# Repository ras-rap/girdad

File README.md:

# GIrDAd

A modern USB-C dongle/device for IrDA SIR.

## What is this?
This is a IrDA VCOM device/dongle port thing, it has USB-C on one end, and an IrDA transceiver on the other.

## Why did you make this
I bought a Cipherlab 8001 Mobile Computer at a thrift store, and I want to program it, but I dont want to buy one of the data cradles for it, as they are way too rare and expensive for some pogo pins and an IrDA transceiver, so now we have this, which can be used for much more than the thing I built it for.

## How do I use it
Well that depends on what you're using it for, but you plug it into your computer, and open up whatever program wants an IrDA SIR port, and use it like you would a device from the late 90's early 2000's

## Specs

- 115.2 kbp/s max transfer rate
- 870-910 nm wavelength
- 1m max usage distance
- 115200 max baud

***Made by Ras_rap for [Hackclub Fallout](https://fallout.hackclub.com/)***

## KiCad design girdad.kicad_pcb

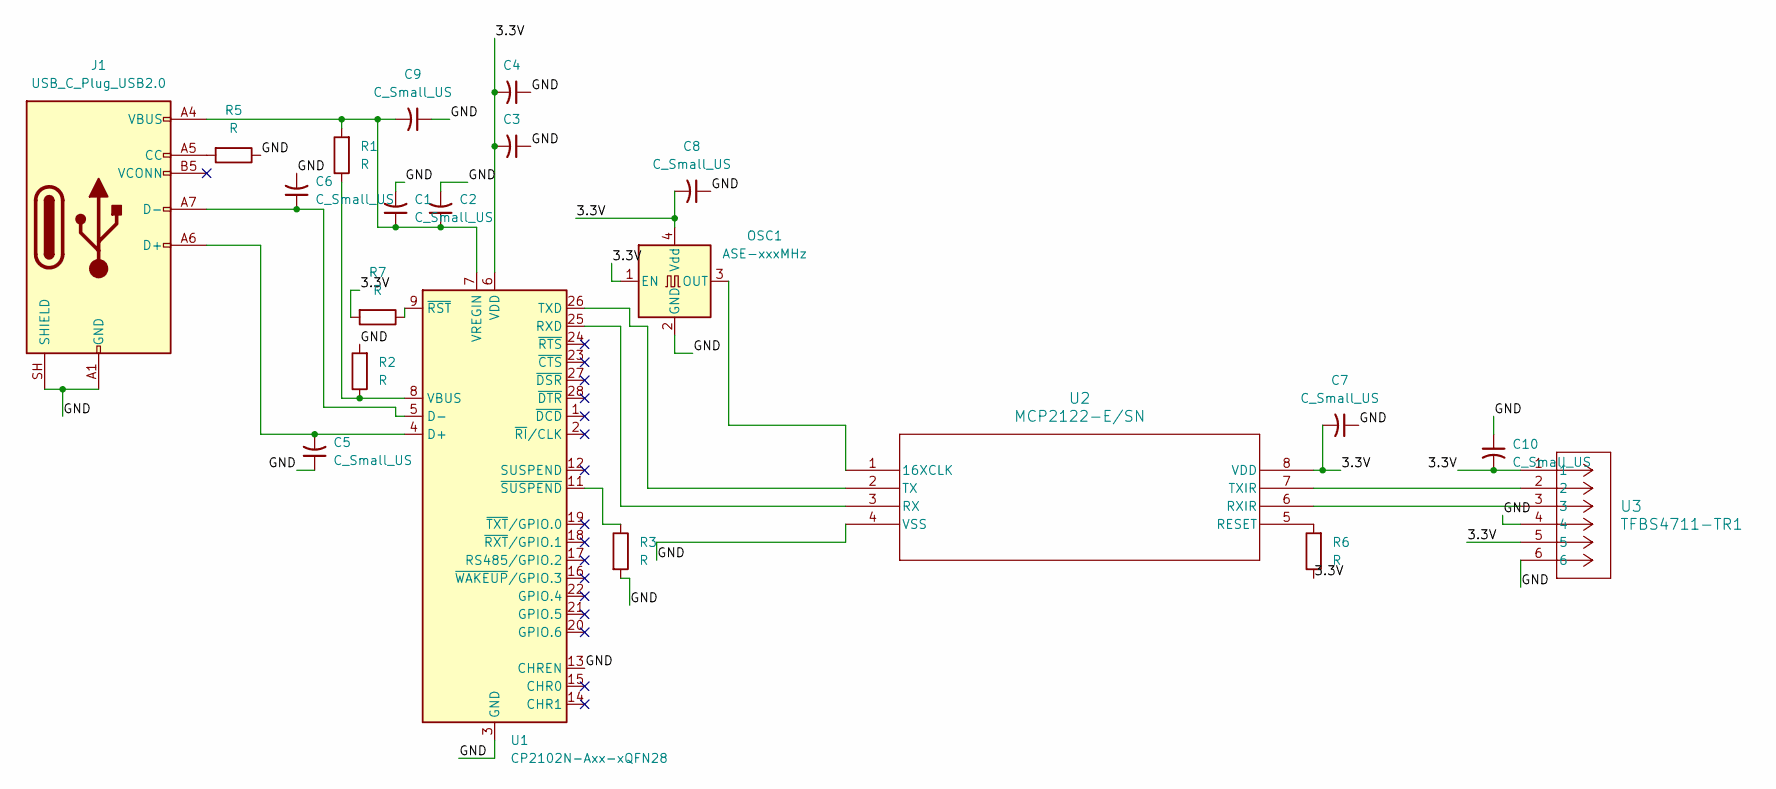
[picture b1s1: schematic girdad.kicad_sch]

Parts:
C1, C2, C3, C4, C5, C6, C7, C8, C9, C10: C_Small_US
J1: USB_C_Plug_USB2.0
OSC1: ASE-xxxMHz; Oscillator_SMD_Abracon_ASE-4Pin_3.2x2.5mm
R1, R2, R3, R5, R6, R7: R
U1: CP2102N-Axx-xQFN28; QFN-28-1EP_5x5mm_P0.5mm_EP3.35x3.35mm
U2: MCP2122-E/SN; SOIC8-N_MC_MCH
U3: TFBS4711-TR1; CONN6_4711-TR1_VIS

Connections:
/3.3V: C3.2, C4.2, C7.2, C8.2, C10.2, OSC1.1 (EN), OSC1.4 (Vdd), R6.1, R7.2, U1.6 (VDD), U2.8 (VDD), U3.1, U3.5
/GND: C1.2, C2.2, C3.1, C4.1, C5.1, C6.2, C7.1, C8.1, C9.1, C10.1, J1.A1 (GND), J1.A12 (GND), J1.B1 (GND), J1.B12 (GND), J1.SH (SHIELD), OSC1.2 (GND), R2.2, R3.2, R5.1, U1.3 (GND), U1.13 (CHREN), U1.29 (GND), U2.4 (VSS), U3.4, U3.6
unnamed: J1.A5 (CC), R5.2
unnamed: C5.2, J1.A6 (D+), U1.4 (D+)
unnamed: C6.1, J1.A7 (D-), U1.5 (D-)
unnamed: OSC1.3 (OUT), U2.1 (16XCLK)
unnamed: U1.25 (RXD), U2.3 (RX)
unnamed: U1.26 (TXD), U2.2 (TX)
unnamed: R1.1, R2.1, U1.8 (VBUS)
unnamed: C1.1, C2.1, C9.2, J1.A4 (VBUS), J1.A9 (VBUS), J1.B4 (VBUS), J1.B9 (VBUS), R1.2, U1.7 (VREGIN)
unnamed: R7.1, U1.9 (~RST)
unnamed: R3.1, U1.11 (~SUSPEND)
unnamed: R6.2, U2.5 (RESET)
unnamed: U2.6 (RXIR), U3.3
unnamed: U2.7 (TXIR), U3.2

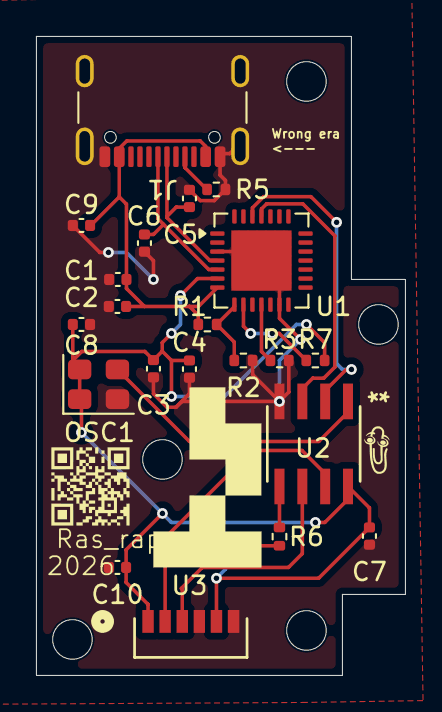
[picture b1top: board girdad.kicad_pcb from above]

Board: 2 copper layers, 20.5 x 35.5 mm, 21 parts (0 on the bottom side), 15 nets.

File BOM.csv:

Reference,Qty,Value,Footprint,Datasheet,Source,Price per unit,Total price
"C1,C3,C7,C8,C10",5,100nF,Capacitor_SMD:C_0402_1005Metric,https://yageogroup.com/content/datasheet/asset/file/KEM_C100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,https://www.digikey.com/en/products/detail/kemet/C0402C104K8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,$0.10,$0.50
C2,1,1UF,Capacitor_SMD:C_0402_1005Metric,https://mm.digikey.com/Volume0/opasdata/d220001/medias/docus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,https://www.digikey.com/en/products/detail/samsung-electro-m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,$0.10,$0.10
C4,2,4.7Uf,Capacitor_SMD:C_0402_1005Metric,https://mm.digikey.com/Volume0/opasdata/d220001/medias/docus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,https://www.digikey.com/en/products/detail/samsung-electro-m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,$0.10,$0.20
"C5,C6",2,100pF,Capacitor_SMD:C_0402_1005Metric,https://mm.digikey.com/Volume0/opasdata/d220001/medias/docus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,https://www.digikey.com/en/products/detail/samsung-electro-m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,$0.10,$0.20
R1,1,47K OHM,Resistor_SMD:R_0402_1005Metric,https://www.te.com/commerce/DocumentDelivery/DDEController?A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,https://www.digikey.com/en/products/detail/te-connectivity-p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,$0.10,$0.10
"R2,R3,R4,R7",4,10K OHM,Resistor_SMD:R_0402_1005Metric,https://yageogroup.com/content/datasheet/asset/file/PYU-RC_G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,https://www.digikey.com/en/products/detail/yageo/RC0402JR-07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,$0.10,$0.40
"R5,R6",2,5.1K OHM,Resistor_SMD:R_0402_1005Metric,https://www.vishay.com/docs/28773/crcwce3.pdf,https://www.digikey.com/en/products/detail/vishay-dale/CRCW0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,$0.10,$0.20
J1,1,USB_C_Plug_USB2.0,Connector_USB:USB_C_Receptacle_GCT_USB4105-xx-A_16P_TopMnt_Horizontal,https://gct.co/files/specs/usb4105-spec.pdf,https://www.digikey.com/en/products/detail/gct/usb4105-gf-a/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,$0.80,$0.80
OSC1,1,ASE-xxxMHz,Oscillator:Oscillator_SMD_Abracon_ASE-4Pin_3.2x2.5mm,https://abracon.com/Oscillators/ASEseries.pdf,https://www.digikey.com/en/products/detail/abracon-llc/ASE-1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,$0.98,$0.98
U1,1,CP2102N-Axx-xQFN28,Package_DFN_QFN:QFN-28-1EP_5x5mm_P0.5mm_EP3.35x3.35mm,https://www.silabs.com/documents/public/data-sheets/cp2102n-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,https://www.digikey.com/en/products/detail/silicon-labs/CP21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,$4.67,$4.67
U2,1,MCP2122-E/SN,MCP2122:SOIC8-N_MC_MCH,https://ww1.microchip.com/downloads/en/DeviceDoc/21894c.pdf,https://www.digikey.com/en/products/detail/microchip-technol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,$1.01,$1.01
U3,1,TFBS4711-TR1,TFBS4711 (2):CONN6_4711-TR1_VIS,https://www.vishay.com/docs/82633/tfbs4711.pdf,https://www.digikey.com/en/products/detail/vishay-semiconduc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,$4.59,$4.59
,,,,,,,
,,,,,,,
,,,,,,,Total component price
,,,,,,,$13.75

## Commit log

2026-05-17 Add git ignore
2026-05-17 Commit all files
2026-05-22 Made the PCB, and the BOM, now to 3d model a case for it
2026-05-23 Add mounting holes and silkscreen images and messages (More to come)
2026-05-24 Enough silkscreen
2026-05-24 I need to use fusion, not onshape
2026-05-25 Fixed a silkscreen thing
2026-05-31 README and zine page
2026-05-31 Fix an image in the readme
2026-05-31 Add f3d files, remove 3d folder
2026-05-31 Remove locks and backups
